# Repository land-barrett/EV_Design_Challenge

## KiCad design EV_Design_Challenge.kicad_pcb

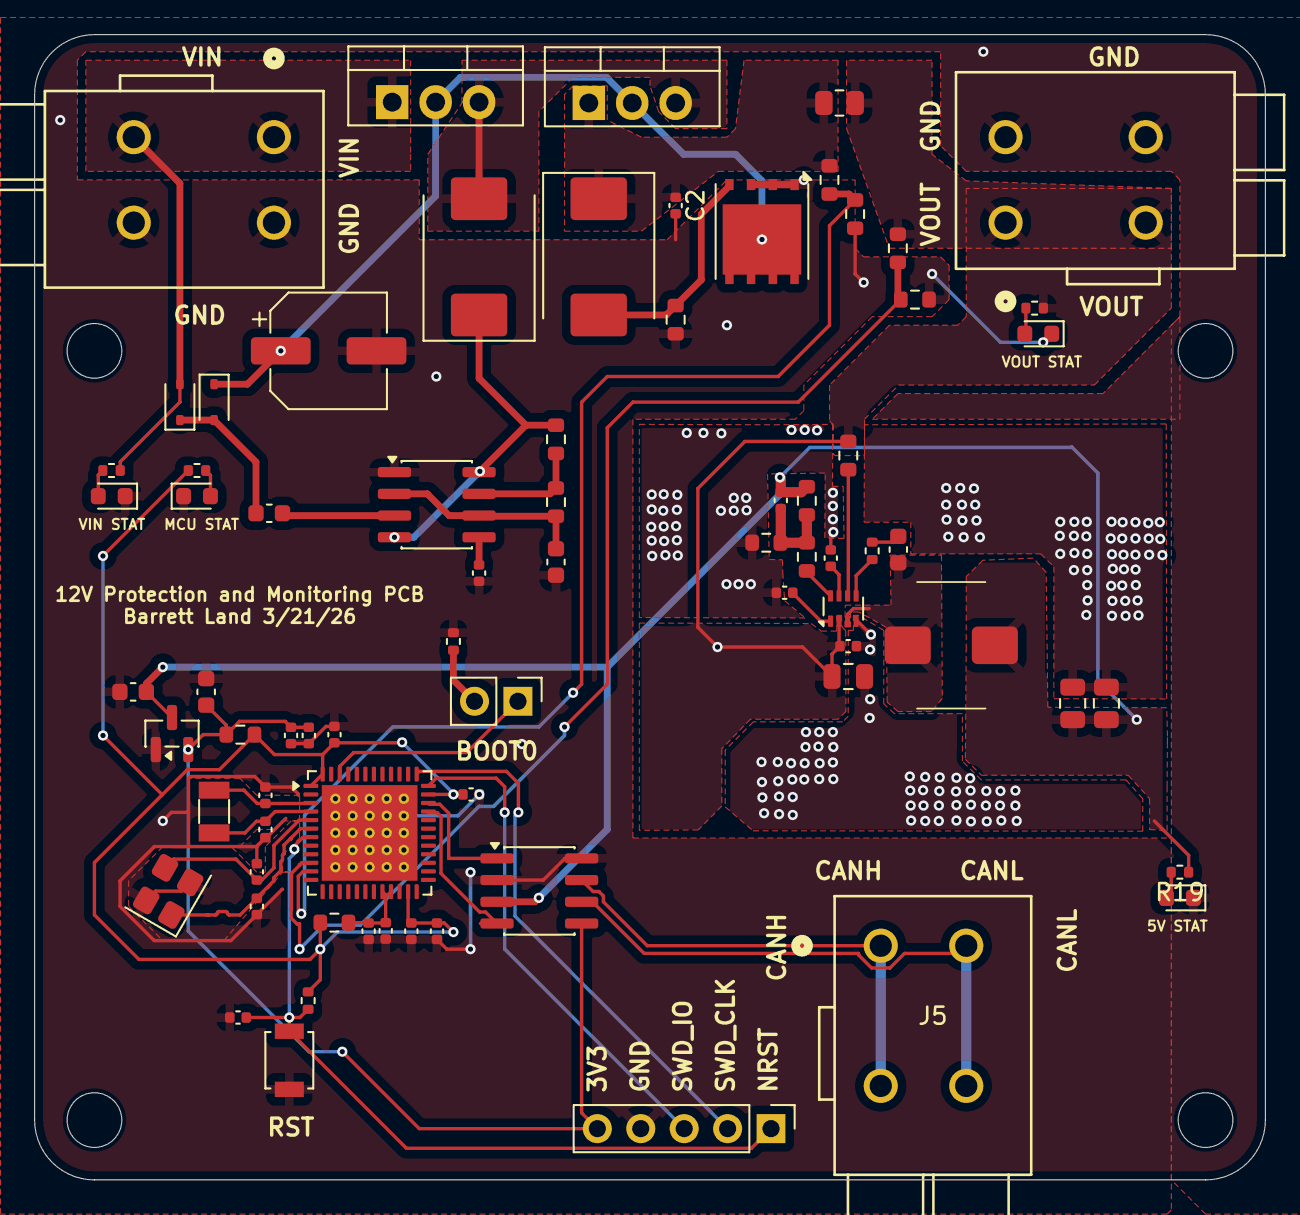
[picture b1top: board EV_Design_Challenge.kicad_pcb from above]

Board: 2 copper layers, 72.0 x 67.0 mm, 78 parts (0 on the bottom side), 45 nets.

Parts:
C1: C_47uF_50V_Electrolytic; CP_Elec_6.3x5.4
C2, C6, C7, C8, C9, C11, C14, C20: C_100nF_0402; C_0402_1005Metric
C3, C12, C23: C_1nF_0402; C_0402_1005Metric
C4: C_47nF_0603; C_0603_1608Metric
C5: C_10uF_0603; C_0603_1608Metric
C10: C_4.7uF_0402; C_0402_1005Metric
C13: C_10nF_0402; C_0402_1005Metric
C15, C16: C_5.1pF_0402; C_0402_1005Metric
C17, C18: C_6.8pF_0402; C_0402_1005Metric
C19, C21#2, C22: C_22uF_0805; C_0805_2012Metric
C21: C_6.8nF_0402; C_0402_1005Metric
C24, C26, C27: C_1uF_0603; C_0603_1608Metric
C28: C_10pF_0402; C_0402_1005Metric
D1, D2: 1N4148WS; D_SOD-323
D3: MBRS1100T3G-FS; D_SMC
D4: LBZT52C12T1G; D_SMC
D5, D7: LED_RED_0603; LED_0603_1608Metric
D6, D8: LED_YELLOW/GREEN_0603; LED_0603_1608Metric
FB1, FB2: BLM18AG601SN1D; R_0603_1608Metric
H1, H2, H3, H4: MountingHole; MountingHole_3.2mm_M3
J1, J2, J5: WAGO-2604-1102; CONN2_2604-1102_WAG
J3: 01x02_2.54mm_Header_Pins; PinHeader_1x02_P2.54mm_Vertical
J4: 01x05_2.54mm_Header_Pins; PinHeader_1x05_P2.54mm_Vertical
L1: L_4.9uH_6.5A_14.5mR_7x6.9; 7x6.9_Wurth_Inductor
Q1, Q2: STP110N10F7; TO-220-3_Vertical
Q3: AON6284A; AO_DFN-8-1EP_5.55x5.2mm_P1.27mm_EP4.12x4.6mm
R1, R2: R_10K_0603_1%; R_0603_1608Metric
R3: R_1.5K_0603_1%; R_0603_1608Metric
R4, R10: R_1.1K_0603_1%; R_0603_1608Metric
R5, R6: R_10K_0402; R_0402_1005Metric
R7, R9: R_16K_0603_1%; R_0603_1608Metric
R8: R_Shunt_10mR_0805_0.5W; R_0805_2012Metric
R11: R_20R_0402; R_0402_1005Metric
R12: R_15K_0603_1%; R_0603_1608Metric
R12#2: R_604K_0603_1%; R_0603_1608Metric
R14: R_7.68K_0603_1%; R_0603_1608Metric
R15: R_40.2K_0603_1%; R_0603_1608Metric
R16, R17: R_5.1K_0402; R_0402_1005Metric
R18, R19: R_1K_0402; R_0402_1005Metric
SW1: SMT_Debug_Push_Button; SW_SPST_B3U-1000P
U1: STM32G473CEUx; QFN-48-1EP_7x7mm_P0.5mm_EP5.6x5.6mm
U2: MP2393GTL-Z; SOT-583-8
U3: NE555DR; SOIC-8_3.9x4.9mm_P1.27mm
U4: MCP2562-E-SN; SOIC-8_3.9x4.9mm_P1.27mm
U5: TPS7A0533PDBZR; SOT-23
Y3: X322524MSB4SI; Crystal_SMD_3225-4Pin_3.2x2.5mm
Y4: ABS07-120-32.768KHZ-T; Crystal_SMD_3215-2Pin_3.2x1.5mm

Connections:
+3V3: C6.1, C7.1, C26.1, FB1.1, J4.5, U4.5 (Vio), U5.2 (VO)
+5V: C21#2.1, C22.1, C27.1, C28.2, L1.1, R15.2, R19.1, U4.3 (VDD), U5.3 (VI)
/Surge Protection/CommSrc: D3.2 (A), Q1.3 (S), Q2.3 (S)
/Surge Protection/Vout_PreShunt: C2.1, D4.1 (K), Q2.1 (D), R8.1, R9.1
ADC1_IN3: R4.1, R7.2, U1.10 (PA2)
ADC1_IN4: R9.2, R10.1, U1.11 (PA3)
CANH: J5.1 (1_1), J5.2 (1_2), U4.7 (CANH)
CANL: J5.3 (2_1), J5.4 (2_2), U4.6 (CANL)
FDCAN1_RX: U1.33 (PA11), U4.4 (RXD)
FDCAN1_TX: U1.34 (PA12), U4.1 (TXD)
GND: C19.2, C20.2, C21.2, C21#2.2, C22.2, C23.1, R14.2, U2.4 (GND)
MCU_GND: C1.2, C2.2, C3.2, C4.2, C6.2, C7.2, C8.2, C9.2, C10.2, C11.2, C12.2, C13.2, C14.1, C15.1, C16.2, C17.2, C18.1, C26.2, C27.2, D5.1 (K), D6.1 (K), D7.1 (K), D8.1 (K), J1.3 (2_1), J1.4 (2_2), J2.3 (2_1), J2.4 (2_2), J4.4, Q3.1 (S), Q3.2 (S), Q3.3 (S), R1.2, R4.2, R5.1, R10.2, SW1.1, U1.49 (VSS), U3.1 (GND), U4.2 (VSS), U4.8 (STBY), U5.1 (GND), Y3.2, Y3.4
MCU_VDD: C8.1, C9.1, C10.1, C11.1, FB1.2, FB2.2, R6.2, R18.1, U1.1 (VBAT), U1.23 (VDD), U1.35 (VDD), U1.48 (VDD)
MCU_VDDA: C12.1, C13.1, FB2.1, U1.20 (VREF+), U1.21 (VDDA)
NRST: C14.2, J4.1, R6.1, SW1.2, U1.7 (PG10)
unnamed: C24.2, R11.1
unnamed: C28.1, R12.2, R14.1, R15.1
unnamed: C5.1, D1.2 (A), D2.1 (K)
unnamed: C1.1, D1.1 (K), Q1.2 (G), Q2.2 (G), Q3.5 (D)
unnamed: D3.1 (K), R3.1, U3.4 (~RST), U3.8 (VCC)
unnamed: D4.2 (A), Q3.4 (G), R1.1
unnamed: D5.2 (A), R19.2
unnamed: D6.2 (A), R17.2
unnamed: D7.2 (A), R16.2
unnamed: D8.2 (A), R18.2
unnamed: J3.1, U1.46 (PB8)
unnamed: J3.2, R5.2
unnamed: R11.2, U2.5 (BST)
unnamed: R12#2.1, U2.6 (EN)
unnamed: R12.1, U2.8 (FB)
unnamed: C23.2, U2.1 (PG)
unnamed: C21.1, U2.7 (SS)
unnamed: C24.1, L1.2, U2.3 (SW)
unnamed: C3.1, U3.5 (CONT)
unnamed: R2.1, R3.2, U3.7 (DISCH)
unnamed: C5.2, U3.3 (OUT)
unnamed: C4.1, R2.2, U3.2 (TRIG), U3.6 (THRES)
OSC32_IN: C15.2, U1.3 (PC14), Y4.2
OSC32_OUT: C16.1, U1.4 (PC15), Y4.1
OSC_IN: C17.1, U1.5 (PF0), Y3.3
OSC_OUT: C18.2, U1.6 (PF1), Y3.1
SWD_CLK: J4.2, U1.37 (PA14)
SWD_IO: J4.3, U1.36 (PA13)
Vin: D2.2 (A), J1.1 (1_1), J1.2 (1_2), Q1.1 (D), R16.1
Vout: C19.1, C20.1, J2.1 (1_1), J2.2 (1_2), R7.1, R8.2, R12#2.2, R17.1, U2.2 (IN)
